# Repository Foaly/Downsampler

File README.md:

Downsampler
===========

This repo contains the files for the Eurorack modular Downsampler created in the WS 17/18 Projekt Labor Course at TU Berlin.
The Eagle file was updated to be more readable. The LTSpice files are now up to date with the latest schematics.
Both the Eagle and LTSpice files contain the latest version from the end of the course.

The contents of this repository are licensed under the [CC-BY-SA 4.0](https://creativecommons.org/licenses/by-sa/4.0/) license unless a file is explicitly marked otherwise.

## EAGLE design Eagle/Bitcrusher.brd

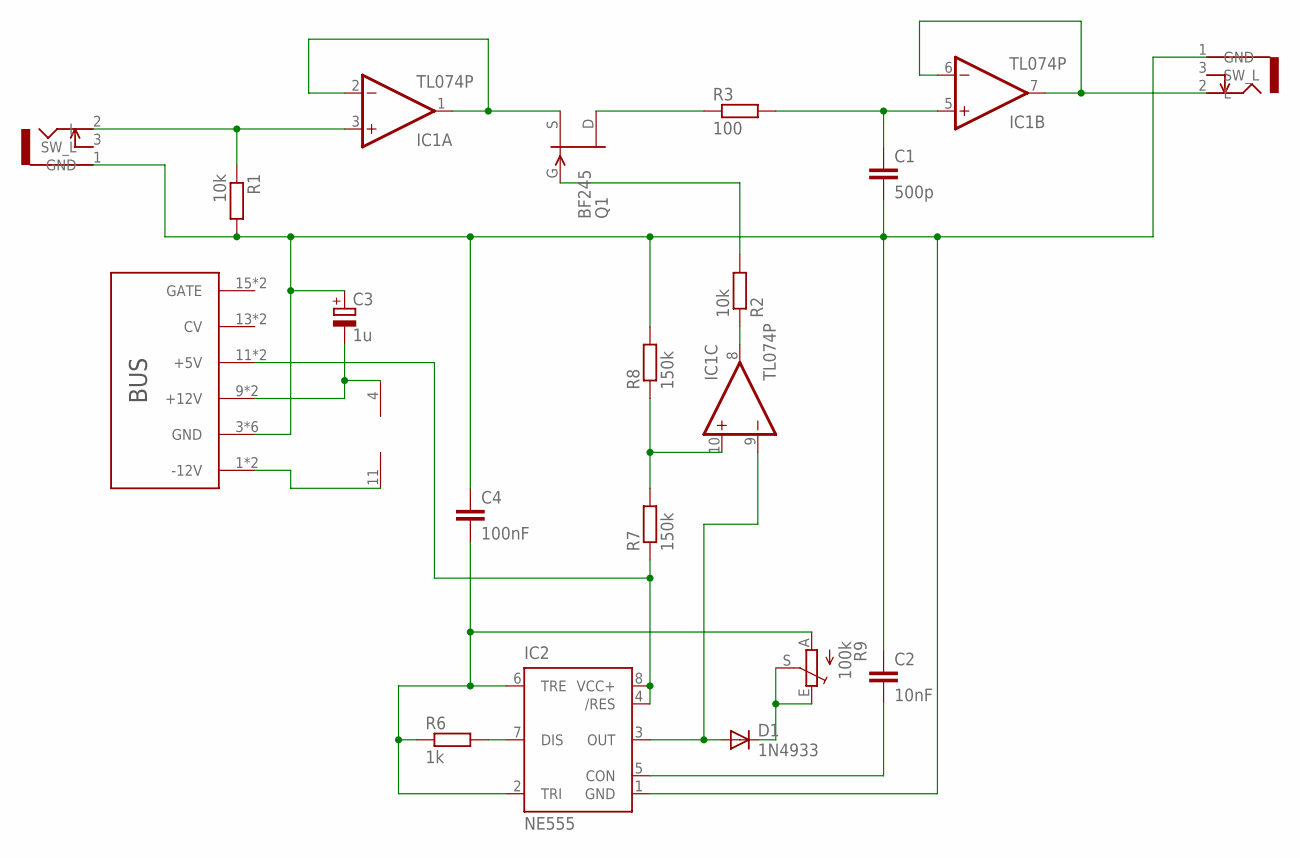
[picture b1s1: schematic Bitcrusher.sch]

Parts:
C1: 500p; C050-024X044
C2: 10nF; C050-024X044
C3: 1u; E5-4
C4: 100nF; C050-024X044
D1: 1N4933; DO41-10
IC1: TL074P; DIL14
IC2: NE555; DIL-08
Q1: BF245; TO92
R1, R2: 10k; 0309/12
R3: 100; 0309/12
R6: 1k; 0309/12
R7, R8: 150k; 0309/12
R9: 100k; CIP20C-6MM
SOUND_INPUT: JC-128-MONO; JC128
SOUND_OUTPUT: JC-128-MONO; JC128
U$1: EURO16EURO_HALF; EURO_HALF

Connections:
unnamed: IC1.1 (OUT), IC1.2 (-IN), Q1.2 (S)
unnamed: IC1.3 (+IN), R1.1, SOUND_INPUT.2 (L)
unnamed: IC2.7 (DIS), R6.2
unnamed: IC1.6 (-IN), IC1.7 (OUT), SOUND_OUTPUT.2 (L)
unnamed: C1.1, IC1.5 (+IN), R3.2
unnamed: Q1.1 (D), R3.1
unnamed: Q1.3 (G), R2.2
unnamed: C3.-, IC1.4 (V+), U$1.9 (+12V), U$1.10 (+12V)
unnamed: IC1.11 (V-), U$1.1 (-12V), U$1.2 (-12V)
unnamed: C1.2, C2.1, C3.+, C4.1, IC2.1 (GND), R1.2, R8.2, SOUND_INPUT.1 (GND), SOUND_OUTPUT.1 (GND), U$1.3 (GND), U$1.4 (GND), U$1.5 (GND), U$1.6 (GND), U$1.7 (GND), U$1.8 (GND)
unnamed: C2.2, IC2.5 (CON)
unnamed: IC1.10 (+IN), R7.2, R8.1
unnamed: IC2.4 (/RES), IC2.8 (VCC+), R7.1, U$1.11 (+5V), U$1.12 (+5V)
unnamed: D1.A, IC1.9 (-IN), IC2.3 (OUT)
unnamed: IC1.8 (OUT), R2.1
unnamed: C4.2, IC2.2 (TRI), IC2.6 (TRE), R6.1, R9.A
unnamed: D1.C, R9.E, R9.S

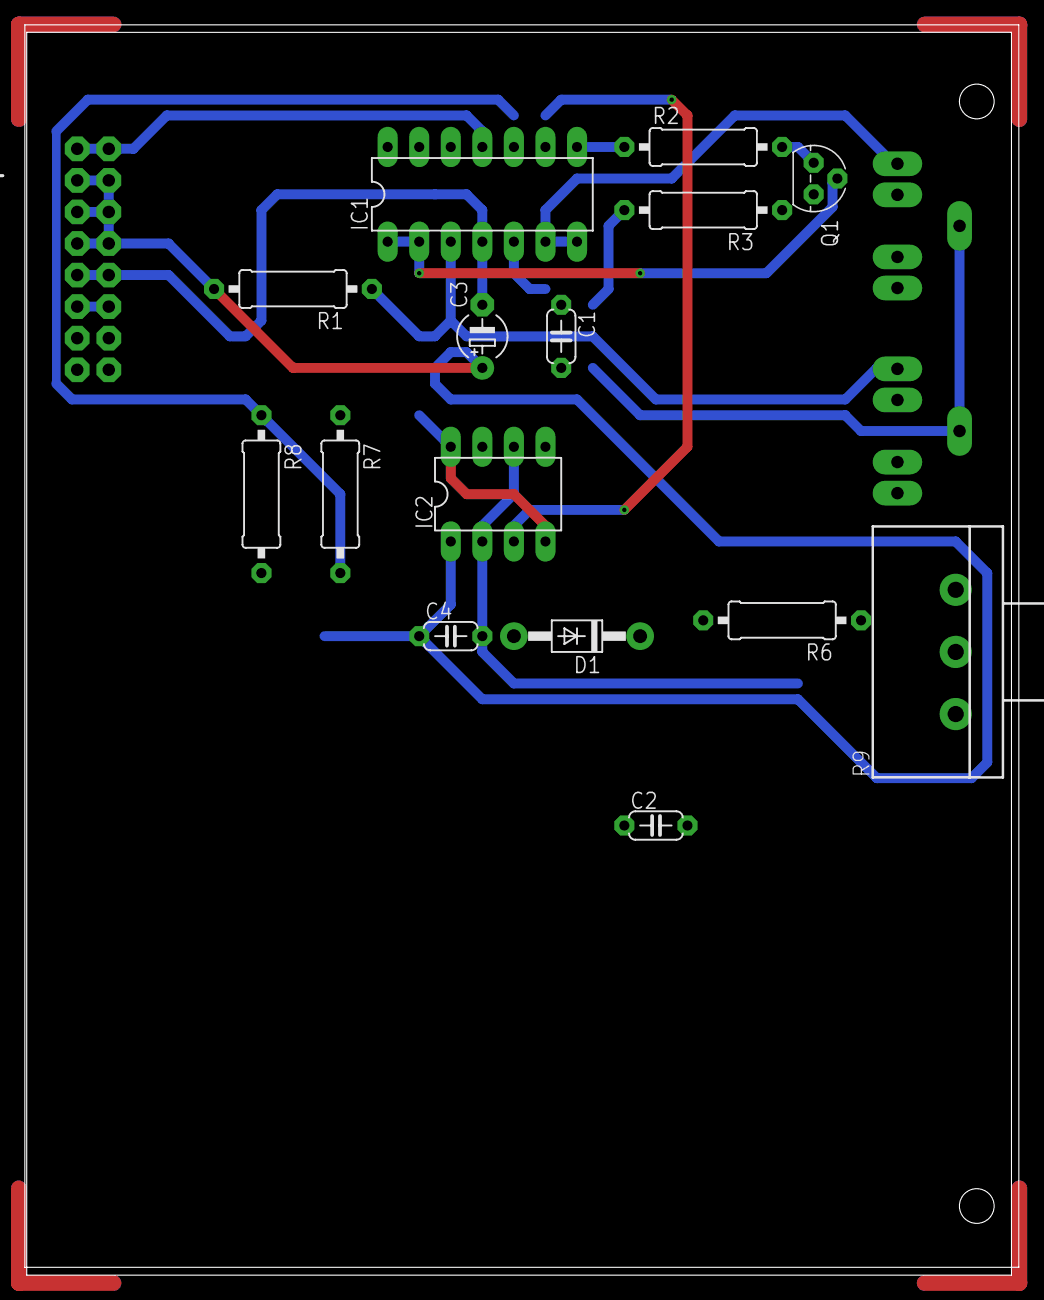
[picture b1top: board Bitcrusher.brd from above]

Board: 2 copper layers, 80.0 x 100.6 mm, 18 parts (0 on the bottom side), 17 nets.

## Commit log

2018-04-19 Initial commit.
2018-04-19 Added LTSpice and Eagle files for the downsampler.
2018-04-19 Added feature ideas.
2018-04-23 Added license notice.
2018-04-23 Added curve.
2018-04-24 Made eagle schematic more readable.
2018-04-24 Changed the LTSpice simulation to be up to date with the latest schematics.
2018-05-18 Added simulation for VC LED blinker and updated feature ideas.
2018-05-18 Removed unnecessary simulation files.
2018-05-19 Added block diagram.
2018-05-19 Added faceplate sketch and moved stuff into faceplate folder.
2018-05-20 Add pure data patch simulating the behavoiur of the downsampler
